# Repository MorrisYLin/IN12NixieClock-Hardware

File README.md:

# IN-12A Nixie Clock Project
## Overview
This PCB contains driver circuitry to handle high-voltage nixie tubes, which allows for binary-coded decimal to select the lit digit and independent PWM dimming for each tube. It also handles power conversion from a 12V 2A wall adapter to 170V, 5V, and 3.3V rails for the nixie tubes, development board, and ICs respectively, and accomodates connections to an ESP8266 WiFi module and an EK-TM4C1294XL development board from TI. These were chosen due to their relevance in my courses, and the design may be easily adapted to smaller microcontrollers more fitting for a clock.
## Images
Final Result

Front Copper

Back Copper

Main Schematic

Tube Driver Schematic

3D Render

## Files
All design was done through KiCAD 8.0, the `TaylorElectronics` folder includes the footprints & symbols for the TES High-voltage power supply as well as others that are not included in the KiCAD standard library. The `nixies_us` folder contains footprints and symbols for the nixie tubes, credit to [judge2005](https://github.com/judge2005/Eagle-and-KiCAD-Nixie-Libs/tree/master) from nixies.us.

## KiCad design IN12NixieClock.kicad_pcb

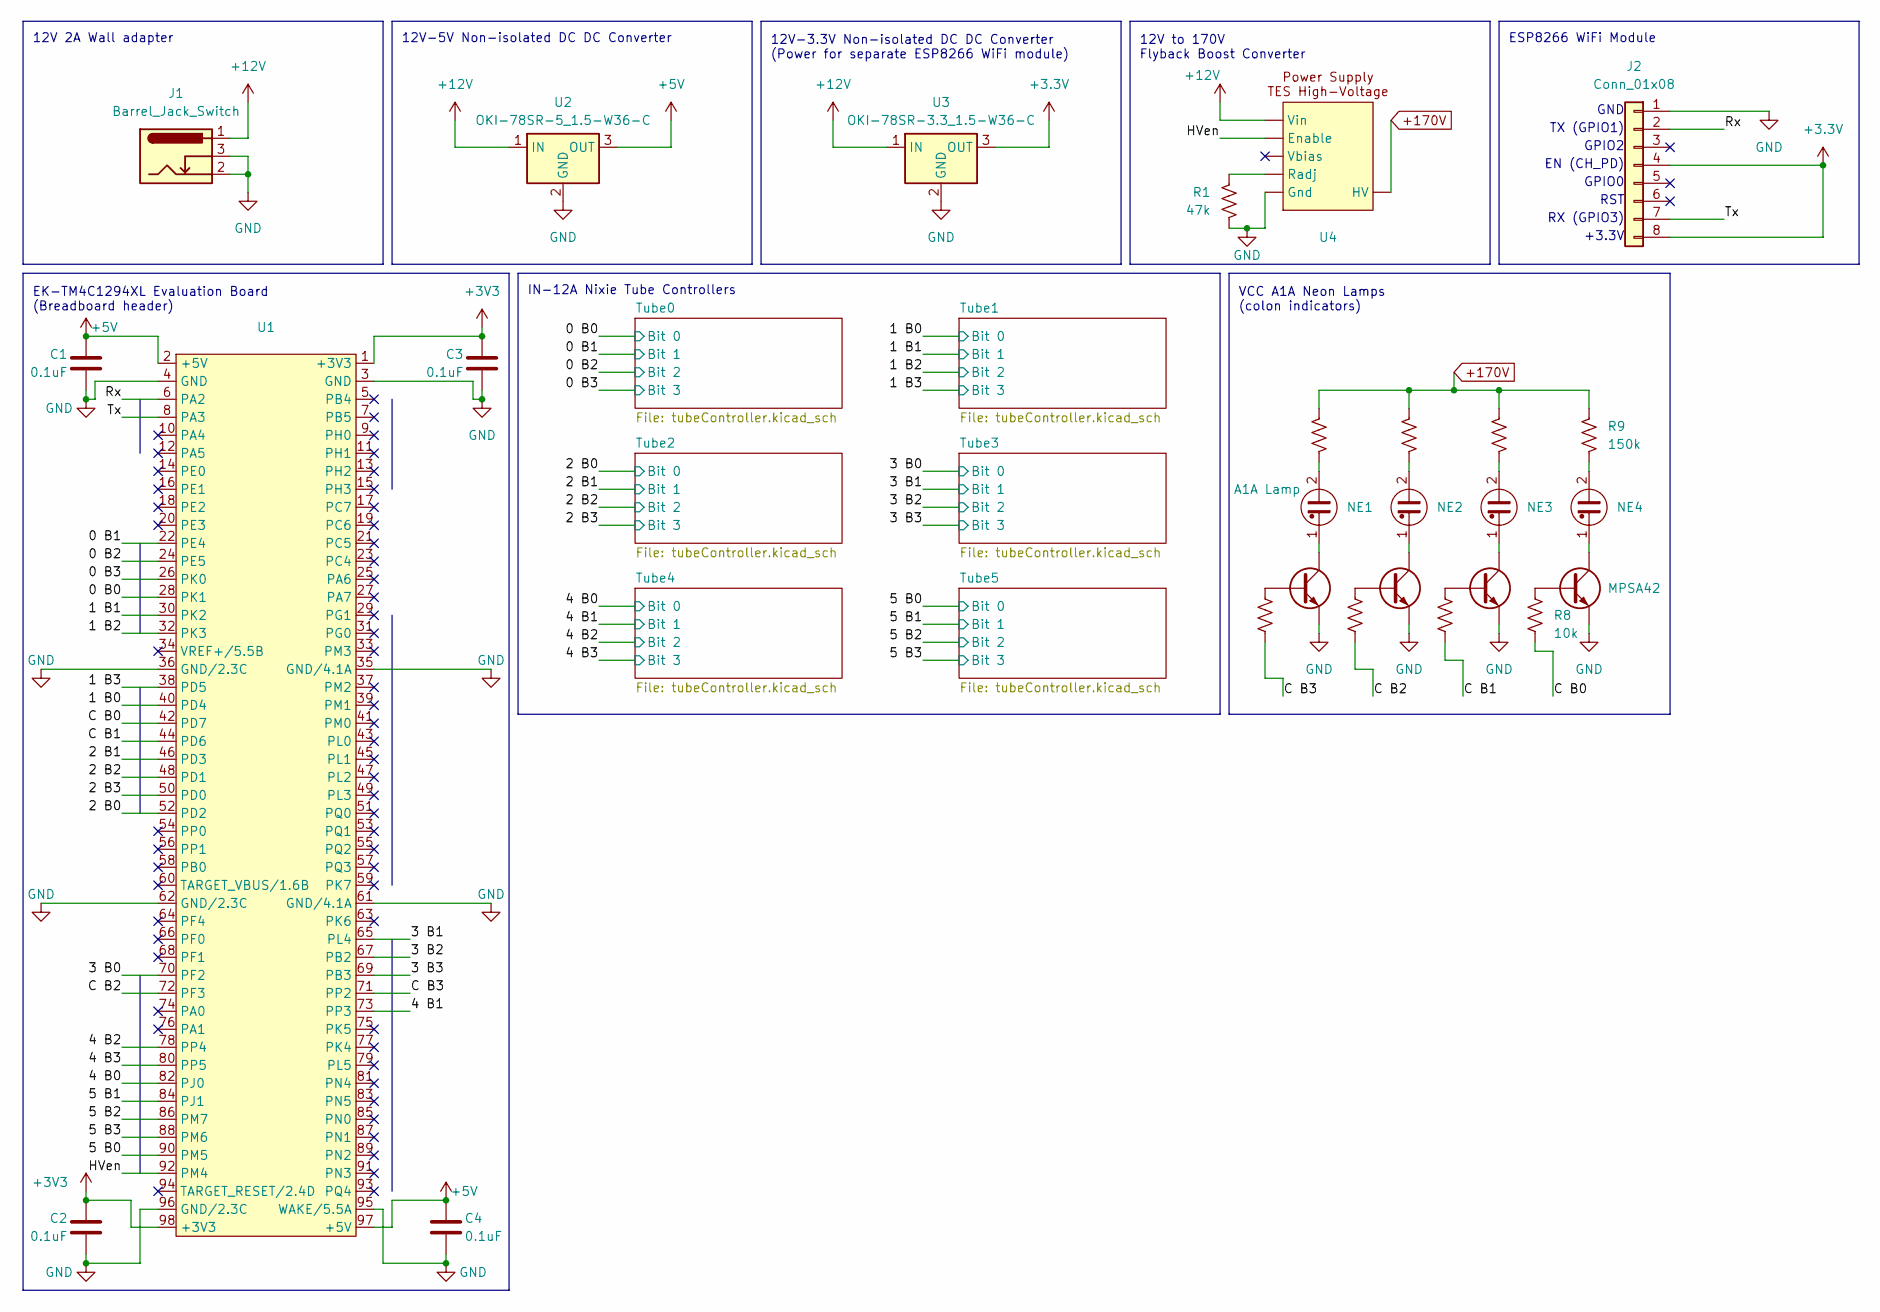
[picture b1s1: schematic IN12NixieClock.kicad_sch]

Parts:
C1, C2, C3, C4: 0.1uF; C_Disc_D5.0mm_W2.5mm_P5.00mm
J1: Barrel_Jack_Switch; 694106301002_1
J2: Conn_01x08; PinSocket_2x04_P2.54mm_Vertical
NE1: A1A Lamp; PinHeader_1x02_P2.54mm_Vertical
NE2, NE3, NE4: Lamp_Neon; PinHeader_1x02_P2.54mm_Vertical
Q1, Q2, Q3, Q4: MPSA42; TO-92_Inline
R1: 47k; R_Axial_DIN0309_L9.0mm_D3.2mm_P12.70mm_Horizontal
R2, R4, R6, R8: 10k; R_Axial_DIN0204_L3.6mm_D1.6mm_P5.08mm_Horizontal
R3, R5, R7, R9: 150k; R_Axial_DIN0309_L9.0mm_D3.2mm_P12.70mm_Horizontal
U1: X11 Breadboard Adapter Interface
U2: OKI-78SR-5_1.5-W36-C; Converter_DCDC_Murata_OKI-78SR_Vertical
U3: OKI-78SR-3.3_1.5-W36-C; Converter_DCDC_Murata_OKI-78SR_Vertical
U4: TES 1363 HVPS Vertical

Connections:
+3.3V: J2.4, J2.8, U3.3 (OUT); also elsewhere on the board
+3V3: C2.1, C3.1, U1.1 (+3V3), U1.98 (+3V3)
+5V: C1.1, C4.1, U1.2 (+5V), U1.97 (+5V), U2.3 (OUT)
+12V: J1.1, U2.1 (IN), U3.1 (IN), U4.Vin
+170V: R3.1, R5.1, R7.1, R9.1, U4.HV; also elsewhere on the board
/0 B0: U1.28 (PK1); also elsewhere on the board
/0 B1: U1.22 (PE4); also elsewhere on the board
/0 B2: U1.24 (PE5); also elsewhere on the board
/0 B3: U1.26 (PK0); also elsewhere on the board
/1 B0: U1.40 (PD4); also elsewhere on the board
/1 B1: U1.30 (PK2); also elsewhere on the board
/1 B2: U1.32 (PK3); also elsewhere on the board
/1 B3: U1.38 (PD5); also elsewhere on the board
/2 B0: U1.52 (PD2); also elsewhere on the board
/2 B1: U1.46 (PD3); also elsewhere on the board
/2 B2: U1.48 (PD1); also elsewhere on the board
/2 B3: U1.50 (PD0); also elsewhere on the board
/3 B0: U1.70 (PF2); also elsewhere on the board
/3 B1: U1.65 (PL4); also elsewhere on the board
/3 B2: U1.67 (PB2); also elsewhere on the board
/3 B3: U1.69 (PB3); also elsewhere on the board
/4 B0: U1.82 (PJ0); also elsewhere on the board
/4 B1: U1.73 (PP3); also elsewhere on the board
/4 B2: U1.78 (PP4); also elsewhere on the board
/4 B3: U1.80 (PP5); also elsewhere on the board
/5 B0: U1.90 (PM5); also elsewhere on the board
/5 B1: U1.84 (PJ1); also elsewhere on the board
/5 B2: U1.86 (PM7); also elsewhere on the board
/5 B3: U1.88 (PM6); also elsewhere on the board
/C B0: R8.2, U1.42 (PD7)
/C B1: R6.2, U1.44 (PD6)
/C B2: R4.2, U1.72 (PF3)
/C B3: R2.2, U1.71 (PP2)
/HVen: U1.92 (PM4), U4.Enable
/Rx: J2.2, U1.6 (PA2)
/Tx: J2.7, U1.8 (PA3)
GND: C1.2, C2.2, C3.2, C4.2, J1.2, J1.3, J2.1, Q1.1 (E), Q2.1 (E), Q3.1 (E), Q4.1 (E), R1.1, U1.3 (GND), U1.4 (GND), U1.35 (GND/4.1A), U1.36 (GND/2.3C), U1.61 (GND/4.1A), U1.62 (GND/2.3C), U1.95 (WAKE/5.5A), U1.96 (GND/2.3C), U2.2 (GND), U3.2 (GND), U4.Gnd; also elsewhere on the board
unnamed: NE1.2, R3.2
unnamed: NE2.2, R5.2
unnamed: NE3.2, R7.2
unnamed: NE4.2, R9.2
unnamed: Q1.2 (B), R2.1
unnamed: NE1.1, Q1.3 (C)
unnamed: Q2.2 (B), R4.1
unnamed: NE2.1, Q2.3 (C)
unnamed: Q3.2 (B), R6.1
unnamed: NE3.1, Q3.3 (C)
unnamed: Q4.2 (B), R8.1
unnamed: NE4.1, Q4.3 (C)
unnamed: R1.2, U4.Radj

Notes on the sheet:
GND
TX (GPIO1)
GPIO2
RX (GPIO3)
12V to 170V Flyback Boost Converter
IN-12A Nixie Tube Controllers
+3.3V
ESP8266 WiFi Module
EN (CH_PD)
EK-TM4C1294XL Evaluation Board (Breadboard header)
GPIO0
12V 2A Wall adapter
12V-5V Non-isolated DC DC Converter
RST
12V-3.3V Non-isolated DC DC Converter (Power for separate ESP8266 WiFi module)
VCC A1A Neon Lamps (colon indicators)

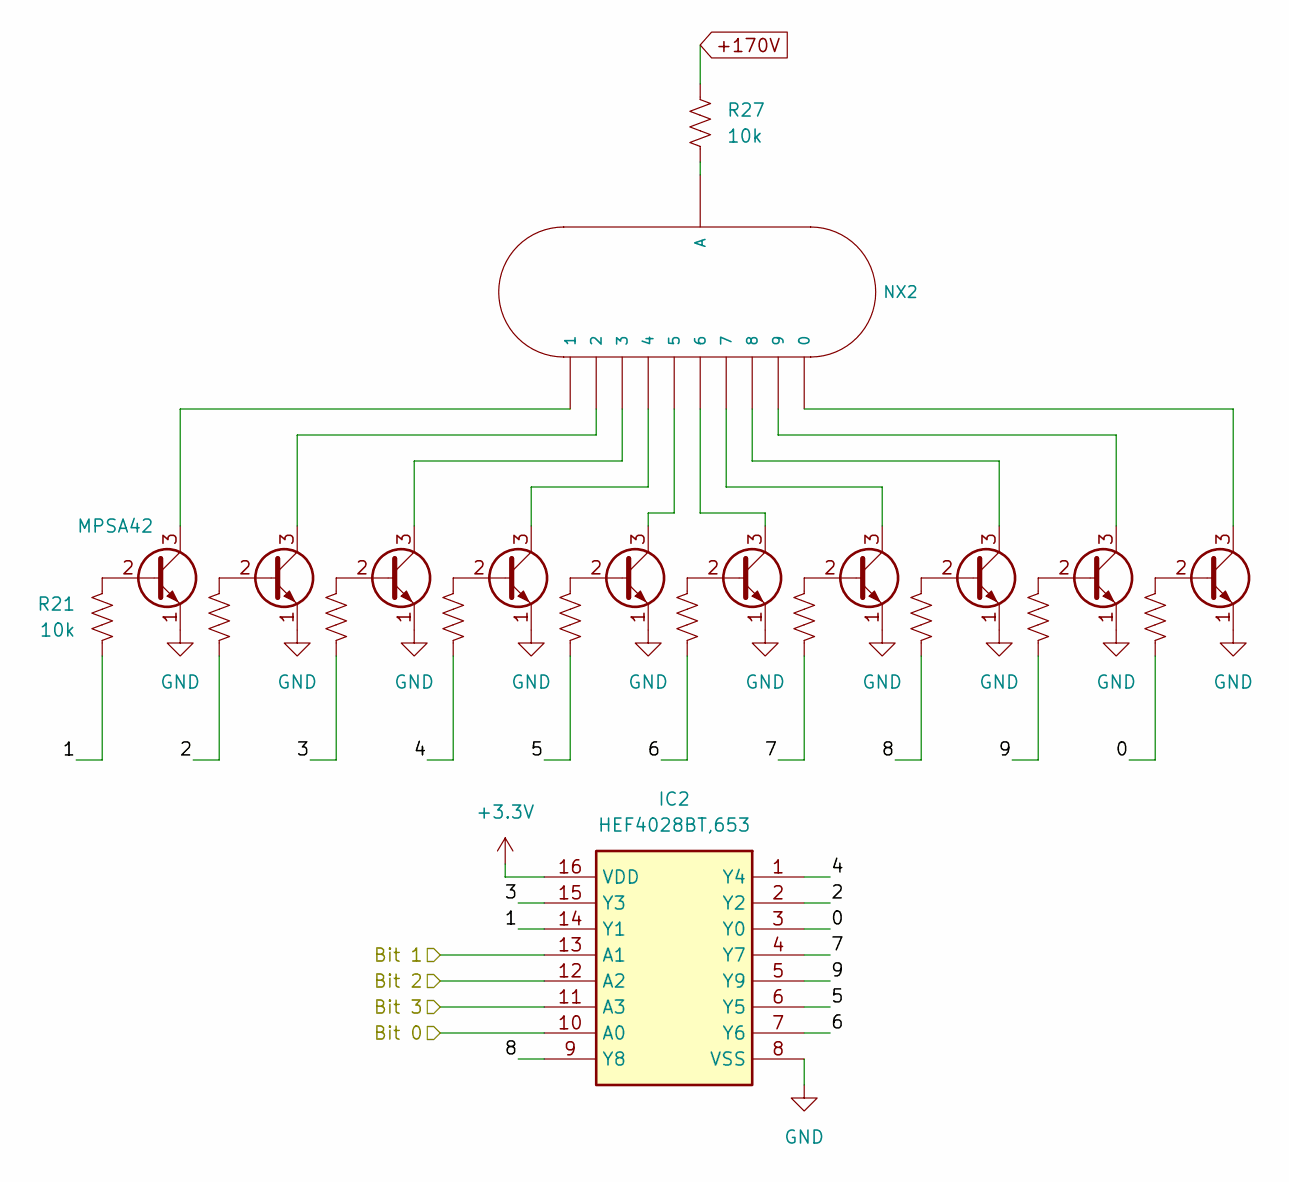
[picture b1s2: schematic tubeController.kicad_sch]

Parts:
IC2: HEF4028BT,653; HEF4028BT653; Mouser Part Number 771-HEF4028BTD-T
NX2: IN-12A; nixies-us-IN-12-DSUB
Q15, Q16, Q17, Q18, Q19, Q20, Q21, Q22, Q23, Q24: MPSA42; TO-92_Inline
R21, R22, R23, R24, R25, R26, R28, R29, R30, R31: 10k; R_Axial_DIN0204_L3.6mm_D1.6mm_P5.08mm_Horizontal
R27: 10k; R_Axial_DIN0309_L9.0mm_D3.2mm_P12.70mm_Horizontal

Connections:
+3.3V: IC2.16 (VDD); also elsewhere on the board
+170V: R27.1; also elsewhere on the board
/1 B0: IC2.10 (A0); also elsewhere on the board
/1 B1: IC2.13 (A1); also elsewhere on the board
/1 B2: IC2.12 (A2); also elsewhere on the board
/1 B3: IC2.11 (A3); also elsewhere on the board
/Tube1/0: IC2.3 (Y0), R31.2
/Tube1/1: IC2.14 (Y1), R21.2
/Tube1/2: IC2.2 (Y2), R22.2
/Tube1/3: IC2.15 (Y3), R23.2
/Tube1/4: IC2.1 (Y4), R24.2
/Tube1/5: IC2.6 (Y5), R25.2
/Tube1/6: IC2.7 (Y6), R26.2
/Tube1/7: IC2.4 (Y7), R28.2
/Tube1/8: IC2.9 (Y8), R29.2
/Tube1/9: IC2.5 (Y9), R30.2
GND: IC2.8 (VSS), Q15.1 (E), Q16.1 (E), Q17.1 (E), Q18.1 (E), Q19.1 (E), Q20.1 (E), Q21.1 (E), Q22.1 (E), Q23.1 (E), Q24.1 (E); also elsewhere on the board
unnamed: NX2.A, R27.2
unnamed: Q15.2 (B), R21.1
unnamed: NX2.1, Q15.3 (C)
unnamed: Q16.2 (B), R22.1
unnamed: NX2.2, Q16.3 (C)
unnamed: Q17.2 (B), R23.1
unnamed: NX2.3, Q17.3 (C)
unnamed: Q18.2 (B), R24.1
unnamed: NX2.4, Q18.3 (C)
unnamed: Q19.2 (B), R25.1
unnamed: NX2.5, Q19.3 (C)
unnamed: Q20.2 (B), R26.1
unnamed: NX2.6, Q20.3 (C)
unnamed: Q21.2 (B), R28.1
unnamed: NX2.7, Q21.3 (C)
unnamed: Q22.2 (B), R29.1
unnamed: NX2.8, Q22.3 (C)
unnamed: Q23.2 (B), R30.1
unnamed: NX2.9, Q23.3 (C)
unnamed: Q24.2 (B), R31.1
unnamed: NX2.0, Q24.3 (C)

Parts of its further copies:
IC1, IC3, IC4, IC5, IC6: HEF4028BT,653; HEF4028BT653; Mouser Part Number 771-HEF4028BTD-T
NX1, NX3, NX4, NX5, NX6: IN-12A; nixies-us-IN-12-DSUB
Q5, Q6, Q7, Q8, Q9, Q10, Q11, Q12, Q13, Q14, Q25, Q26, Q27, Q28, Q29, Q30, Q31, Q32, Q33, Q34, Q35, Q36, Q37, Q38, Q39, Q40, Q41, Q42, Q43, Q44, Q45, Q46, Q47, Q48, Q49, Q50, Q51, Q52, Q53, Q54, Q55, Q56, Q57, Q58, Q59, Q60, Q61, Q62, Q63, Q64: MPSA42; TO-92_Inline
R10, R11, R12, R13, R14, R15, R17, R18, R19, R20, R32, R33, R34, R35, R36, R37, R39, R40, R41, R42, R43, R44, R45, R46, R47, R48, R50, R51, R52, R53, R54, R55, R56, R57, R58, R59, R61, R62, R63, R64, R65, R66, R67, R68, R69, R70, R72, R73, R74, R75: 10k; R_Axial_DIN0204_L3.6mm_D1.6mm_P5.08mm_Horizontal
R16, R38, R49, R60, R71: 10k; R_Axial_DIN0309_L9.0mm_D3.2mm_P12.70mm_Horizontal

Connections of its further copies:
+3.3V: IC1.16 (VDD), IC3.16 (VDD), IC4.16 (VDD), IC5.16 (VDD), IC6.16 (VDD); also elsewhere on the board
+170V: R16.1, R38.1, R49.1, R60.1, R71.1; also elsewhere on the board
/0 B0: IC1.10 (A0); also elsewhere on the board
/0 B1: IC1.13 (A1); also elsewhere on the board
/0 B2: IC1.12 (A2); also elsewhere on the board
/0 B3: IC1.11 (A3); also elsewhere on the board
/2 B0: IC3.10 (A0); also elsewhere on the board
/2 B1: IC3.13 (A1); also elsewhere on the board
/2 B2: IC3.12 (A2); also elsewhere on the board
/2 B3: IC3.11 (A3); also elsewhere on the board
/3 B0: IC4.10 (A0); also elsewhere on the board
/3 B1: IC4.13 (A1); also elsewhere on the board
/3 B2: IC4.12 (A2); also elsewhere on the board
/3 B3: IC4.11 (A3); also elsewhere on the board
/4 B0: IC5.10 (A0); also elsewhere on the board
/4 B1: IC5.13 (A1); also elsewhere on the board
/4 B2: IC5.12 (A2); also elsewhere on the board
/4 B3: IC5.11 (A3); also elsewhere on the board
/5 B0: IC6.10 (A0); also elsewhere on the board
/5 B1: IC6.13 (A1); also elsewhere on the board
/5 B2: IC6.12 (A2); also elsewhere on the board
/5 B3: IC6.11 (A3); also elsewhere on the board
/Tube0/0: IC1.3 (Y0), R20.2
/Tube0/1: IC1.14 (Y1), R10.2
/Tube0/2: IC1.2 (Y2), R11.2
/Tube0/3: IC1.15 (Y3), R12.2
/Tube0/4: IC1.1 (Y4), R13.2
/Tube0/5: IC1.6 (Y5), R14.2
/Tube0/6: IC1.7 (Y6), R15.2
/Tube0/7: IC1.4 (Y7), R17.2
/Tube0/8: IC1.9 (Y8), R18.2
/Tube0/9: IC1.5 (Y9), R19.2
/Tube2/0: IC3.3 (Y0), R42.2
/Tube2/1: IC3.14 (Y1), R32.2
/Tube2/2: IC3.2 (Y2), R33.2
/Tube2/3: IC3.15 (Y3), R34.2
/Tube2/4: IC3.1 (Y4), R35.2
/Tube2/5: IC3.6 (Y5), R36.2
/Tube2/6: IC3.7 (Y6), R37.2
/Tube2/7: IC3.4 (Y7), R39.2
/Tube2/8: IC3.9 (Y8), R40.2
/Tube2/9: IC3.5 (Y9), R41.2
/Tube3/0: IC4.3 (Y0), R53.2
/Tube3/1: IC4.14 (Y1), R43.2
/Tube3/2: IC4.2 (Y2), R44.2
/Tube3/3: IC4.15 (Y3), R45.2
/Tube3/4: IC4.1 (Y4), R46.2
/Tube3/5: IC4.6 (Y5), R47.2
/Tube3/6: IC4.7 (Y6), R48.2
/Tube3/7: IC4.4 (Y7), R50.2
/Tube3/8: IC4.9 (Y8), R51.2
/Tube3/9: IC4.5 (Y9), R52.2
/Tube4/0: IC5.3 (Y0), R64.2
/Tube4/1: IC5.14 (Y1), R54.2
/Tube4/2: IC5.2 (Y2), R55.2
/Tube4/3: IC5.15 (Y3), R56.2
/Tube4/4: IC5.1 (Y4), R57.2
/Tube4/5: IC5.6 (Y5), R58.2
/Tube4/6: IC5.7 (Y6), R59.2
/Tube4/7: IC5.4 (Y7), R61.2
/Tube4/8: IC5.9 (Y8), R62.2
/Tube4/9: IC5.5 (Y9), R63.2
/Tube5/0: IC6.3 (Y0), R75.2
/Tube5/1: IC6.14 (Y1), R65.2
/Tube5/2: IC6.2 (Y2), R66.2
/Tube5/3: IC6.15 (Y3), R67.2
/Tube5/4: IC6.1 (Y4), R68.2
/Tube5/5: IC6.6 (Y5), R69.2
/Tube5/6: IC6.7 (Y6), R70.2
/Tube5/7: IC6.4 (Y7), R72.2
/Tube5/8: IC6.9 (Y8), R73.2
/Tube5/9: IC6.5 (Y9), R74.2
GND: IC1.8 (VSS), IC3.8 (VSS), IC4.8 (VSS), IC5.8 (VSS), IC6.8 (VSS), Q5.1 (E), Q6.1 (E), Q7.1 (E), Q8.1 (E), Q9.1 (E), Q10.1 (E), Q11.1 (E), Q12.1 (E), Q13.1 (E), Q14.1 (E), Q25.1 (E), Q26.1 (E), Q27.1 (E), Q28.1 (E), Q29.1 (E), Q30.1 (E), Q31.1 (E), Q32.1 (E), Q33.1 (E), Q34.1 (E), Q35.1 (E), Q36.1 (E), Q37.1 (E), Q38.1 (E), Q39.1 (E), Q40.1 (E), Q41.1 (E), Q42.1 (E), Q43.1 (E), Q44.1 (E), Q45.1 (E), Q46.1 (E), Q47.1 (E), Q48.1 (E), Q49.1 (E), Q50.1 (E), Q51.1 (E), Q52.1 (E), Q53.1 (E), Q54.1 (E), Q55.1 (E), Q56.1 (E), Q57.1 (E), Q58.1 (E), Q59.1 (E), Q60.1 (E), Q61.1 (E), Q62.1 (E), Q63.1 (E), Q64.1 (E); also elsewhere on the board
unnamed: NX1.A, R16.2
unnamed: NX3.A, R38.2
unnamed: NX4.A, R49.2
unnamed: NX5.A, R60.2
unnamed: NX6.A, R71.2
unnamed: Q5.2 (B), R10.1
unnamed: NX1.1, Q5.3 (C)
unnamed: Q6.2 (B), R11.1
unnamed: NX1.2, Q6.3 (C)
unnamed: Q7.2 (B), R12.1
unnamed: NX1.3, Q7.3 (C)
unnamed: Q8.2 (B), R13.1
unnamed: NX1.4, Q8.3 (C)
unnamed: Q9.2 (B), R14.1
unnamed: NX1.5, Q9.3 (C)
unnamed: Q10.2 (B), R15.1
unnamed: NX1.6, Q10.3 (C)
unnamed: Q11.2 (B), R17.1
unnamed: NX1.7, Q11.3 (C)
unnamed: Q12.2 (B), R18.1
unnamed: NX1.8, Q12.3 (C)
unnamed: Q13.2 (B), R19.1
unnamed: NX1.9, Q13.3 (C)
unnamed: Q14.2 (B), R20.1
unnamed: NX1.0, Q14.3 (C)
unnamed: Q25.2 (B), R32.1
unnamed: NX3.1, Q25.3 (C)
unnamed: Q26.2 (B), R33.1
unnamed: NX3.2, Q26.3 (C)
unnamed: Q27.2 (B), R34.1
unnamed: NX3.3, Q27.3 (C)
unnamed: Q28.2 (B), R35.1
unnamed: NX3.4, Q28.3 (C)
unnamed: Q29.2 (B), R36.1
unnamed: NX3.5, Q29.3 (C)
unnamed: Q30.2 (B), R37.1
unnamed: NX3.6, Q30.3 (C)
unnamed: Q31.2 (B), R39.1
unnamed: NX3.7, Q31.3 (C)
unnamed: Q32.2 (B), R40.1
unnamed: NX3.8, Q32.3 (C)
unnamed: Q33.2 (B), R41.1
unnamed: NX3.9, Q33.3 (C)
unnamed: Q34.2 (B), R42.1
unnamed: NX3.0, Q34.3 (C)
unnamed: Q35.2 (B), R43.1
unnamed: NX4.1, Q35.3 (C)
unnamed: Q36.2 (B), R44.1
unnamed: NX4.2, Q36.3 (C)
unnamed: Q37.2 (B), R45.1
unnamed: NX4.3, Q37.3 (C)
unnamed: Q38.2 (B), R46.1
unnamed: NX4.4, Q38.3 (C)
unnamed: Q39.2 (B), R47.1
unnamed: NX4.5, Q39.3 (C)
unnamed: Q40.2 (B), R48.1
unnamed: NX4.6, Q40.3 (C)
unnamed: Q41.2 (B), R50.1
unnamed: NX4.7, Q41.3 (C)
unnamed: Q42.2 (B), R51.1
unnamed: NX4.8, Q42.3 (C)
unnamed: Q43.2 (B), R52.1
unnamed: NX4.9, Q43.3 (C)
unnamed: Q44.2 (B), R53.1
unnamed: NX4.0, Q44.3 (C)
unnamed: Q45.2 (B), R54.1
unnamed: NX5.1, Q45.3 (C)
unnamed: Q46.2 (B), R55.1
unnamed: NX5.2, Q46.3 (C)
unnamed: Q47.2 (B), R56.1
unnamed: NX5.3, Q47.3 (C)
unnamed: Q48.2 (B), R57.1
unnamed: NX5.4, Q48.3 (C)
unnamed: Q49.2 (B), R58.1
unnamed: NX5.5, Q49.3 (C)
unnamed: Q50.2 (B), R59.1
unnamed: NX5.6, Q50.3 (C)
unnamed: Q51.2 (B), R61.1
unnamed: NX5.7, Q51.3 (C)
unnamed: Q52.2 (B), R62.1
unnamed: NX5.8, Q52.3 (C)
unnamed: Q53.2 (B), R63.1
unnamed: NX5.9, Q53.3 (C)
unnamed: Q54.2 (B), R64.1
unnamed: NX5.0, Q54.3 (C)
unnamed: Q55.2 (B), R65.1
unnamed: NX6.1, Q55.3 (C)
unnamed: Q56.2 (B), R66.1
unnamed: NX6.2, Q56.3 (C)
unnamed: Q57.2 (B), R67.1
unnamed: NX6.3, Q57.3 (C)
unnamed: Q58.2 (B), R68.1
unnamed: NX6.4, Q58.3 (C)
unnamed: Q59.2 (B), R69.1
unnamed: NX6.5, Q59.3 (C)
unnamed: Q60.2 (B), R70.1
unnamed: NX6.6, Q60.3 (C)
unnamed: Q61.2 (B), R72.1
unnamed: NX6.7, Q61.3 (C)
unnamed: Q62.2 (B), R73.1
unnamed: NX6.8, Q62.3 (C)
unnamed: Q63.2 (B), R74.1
unnamed: NX6.9, Q63.3 (C)
unnamed: Q64.2 (B), R75.1
unnamed: NX6.0, Q64.3 (C)

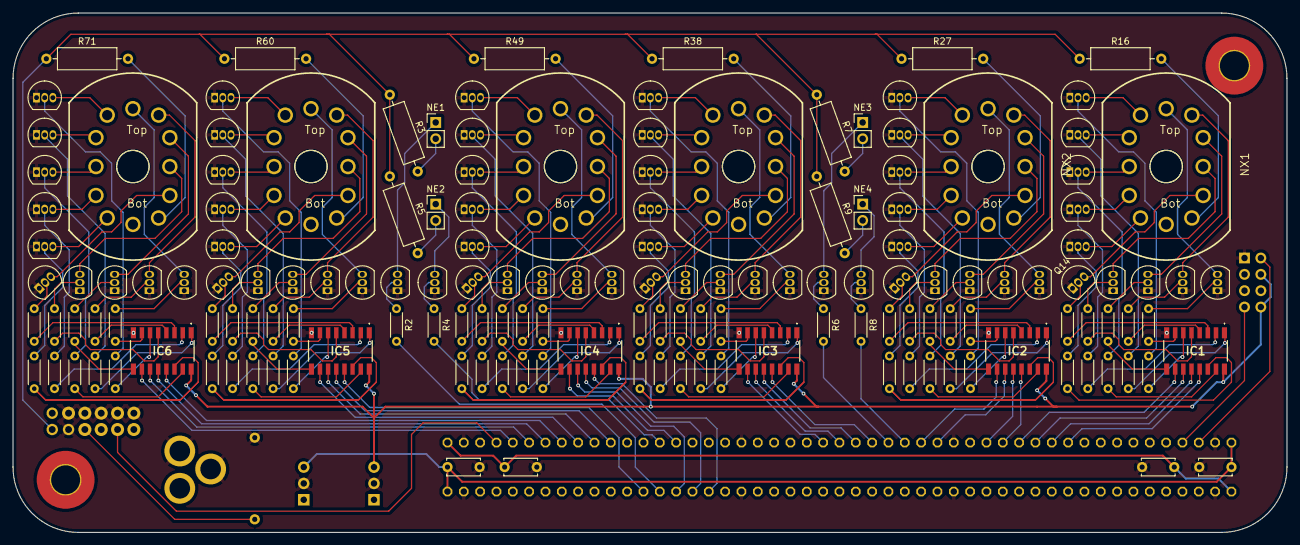
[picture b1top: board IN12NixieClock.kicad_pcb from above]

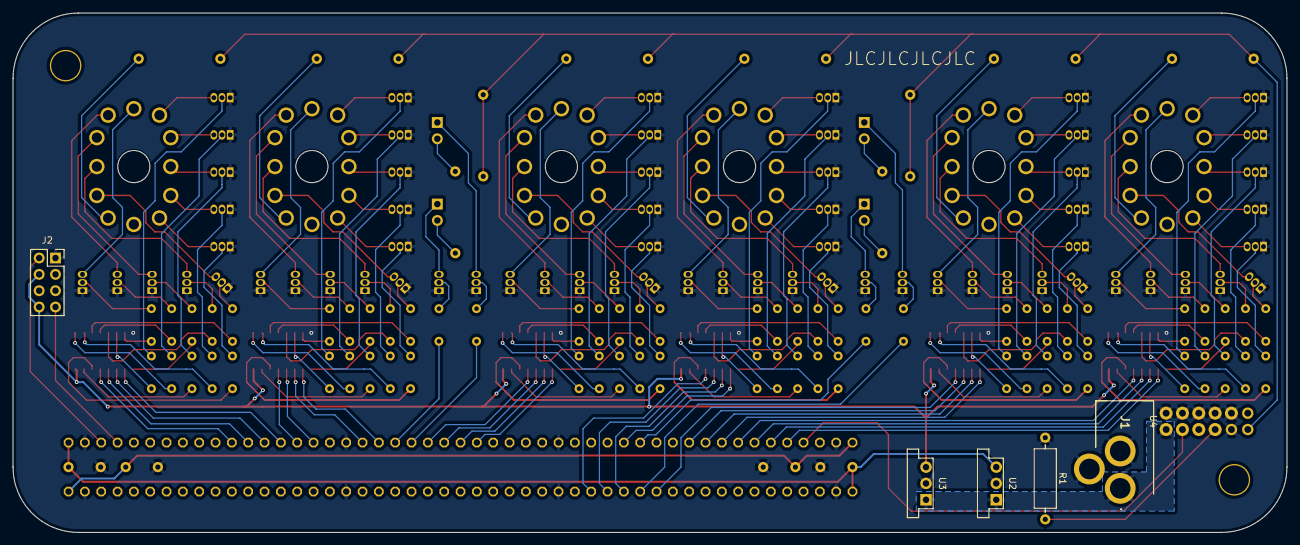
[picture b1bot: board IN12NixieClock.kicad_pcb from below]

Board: 2 copper layers, 198.1 x 80.8 mm, 165 parts (6 on the bottom side), 236 nets.

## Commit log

2024-09-02 Added project files and needed symbols/footprints
2024-09-02 Added reference image
2024-09-02 Removed image
